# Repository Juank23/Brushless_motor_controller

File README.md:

# Brushless Motor Controller
This repository contains the hardware and software implementation of a brushless 
motor controller based on the [Espressif ESP32 module].

The schematic and PCB was designed using de EDA tool [KiCad] and all C++ 
code was compiled using the [Espressif ESP32 toolchain].

## Brushless Motor Controller Schematic
![][bm_controller_sch]

[bm_controller_sch]: https://github.com/fabriziotappero/Brushless_motor_controller/blob/master/PCB/bm_controller_sch.png ""
[Espressif ESP32 module]: https://www.espressif.com/en/products/hardware/development-boards
[Espressif ESP32 toolchain]: https://dl.espressif.com/doc/esp-idf/latest/index.html
[KiCad]: http://kicad-pcb.org/

## Hardware And Software Tools

Install **Kicad 5** on Debial-like Linux systems:
```
sudo add-apt-repository --yes ppa:js-reynaud/kicad-5
sudo apt-get update
sudo apt-get install kicad kicad-libraries
```

Install **ESP32 Espressif** compiler with its dependencies:
```
sudo apt-get install git wget make libncurses-dev flex bison gperf python python-serial

wget https://dl.espressif.com/dl/xtensa-esp32-elf-linux64-1.22.0-80-g6c4433a-5.2.0.tar.gz

tar -xvf xtensa-esp32-elf-linux64-1.22.0-80-g6c4433a-5.2.0.tar.gz
sudo mv xtensa-esp32-elf /opt
export PATH=/opt/xtensa-esp32-elf/bin:$PATH
```
Install the **ESP32 Espressif** developing environment IDF:
```
mkdir /opt/eps32 
cd /opt/eps32
git clone --recursive https://github.com/espressif/esp-idf.git
cd esp-idf
git submodule update --init
export IDF_PATH=/opt/esp32/esp-idf
```

Begin from a simple example:
```
git clone https://github.com/espressif/esp-idf-template.git myapp
cd myapp
make menuconfig
```
A lot of code examples in ```/opt/esp32/esp-idf/examples```. For more information refer to the [Espressif ESP32 Programming Guide]

[Espressif ESP32 Programming Guide]: https://dl.espressif.com/doc/esp-idf/latest/index.html

## References

[Espressif ESP32 Programming Guide](https://dl.espressif.com/doc/esp-idf/latest/index.html)

[Digi-Key An Introduction to Brushless DC Motor Control](https://www.digikey.com/en/articles/techzone/2013/mar/an-introduction-to-brushless-dc-motor-control)

## More Information
For any enquiry contact:

fabrizio.tappero@gmail.com

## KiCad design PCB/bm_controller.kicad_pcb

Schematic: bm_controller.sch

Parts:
C1, C2: 4.7uF; C_1210_3225Metric; Mouser 963-HMK325C7475MM-PE
C3: 1uF; C_0603_1608Metric
C4, C7: 0.01uF; C_0603_1608Metric
C5, C6: 22uF; C_0603_1608Metric; Mouser 810-C1608X5R1A226M
D1: V1PM15-M3/H; D_PowerDI-123; Mouser 78-V1PM15-M3/H
D2: APHD1608LCGCK; LED_0603_1608Metric; Mouser 604-APHD1608LCGCK
J1: Conn_01x08; PinSocket_1x08_P2.54mm_Vertical
J2: Conn_01x03; PinSocket_1x03_P2.54mm_Vertical
L1: 220uH; L_Taiyo-Yuden_NR-60xx; MPN VLS6045EX221MCA; Mouser 810-VLS6045EX221MCA
Q1: BSC040N10NS5; TDSON-8-1; Mouser 726-BSC040N10NS5
R1: 121k; R_0603_1608Metric
R2: 8.25k; R_0603_1608Metric
R3: 43.2k; R_0603_1608Metric
R4: 15k; R_0603_1608Metric
R5: 4.32k; R_0603_1608Metric
R6: 1M; R_0603_1608Metric
R7: 1k; R_0603_1608Metric
RV1: 100k; Potentiometer_Bourns_3214W_Vertical; Mouser 81-PVG3A104C01R00
TP1, TP2: none; TestPoint_Pad_D1.0mm
U1: ESP32-DOIT-EVALKIT
U2: IRS2890DS; SOIC-14_3.9x8.7mm_P1.27mm; Mouser 726-IRS2890DSTRPBF
U3: LM5017MR; SOIC-8-1EP_3.9x4.9mm_P1.27mm_EP2.35x2.35mm; MPN LM5017MRX/NOPB; Mouser 926-LM5017MRX/NOPB
U4: LMT87DCK; SOT-353_SC-70-5

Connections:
5V: C5.1, C6.1, L1.2, R4.2, RV1.1, TP2.1, U4.1, U4.4, U4.5
GND: C1.2, C2.2, C3.2, C5.2, C6.2, C7.1, R2.1, R5.1, R6.1, R7.1, RV1.3, U3.1, U3.9, U4.2
unnamed: C1.1, C2.1, D1.1, R1.2, R3.2, TP1.1, U3.2
unnamed: C3.1, U3.6
unnamed: C4.1, L1.1, U3.8
unnamed: C4.2, U3.7
unnamed: D2.1, R7.2
unnamed: D2.2, U1.20
unnamed: Q1.1 (S), Q1.2 (S), Q1.3 (S)
unnamed: R1.1, R2.2, U3.3
unnamed: R3.1, U3.4
unnamed: R4.1, R5.2, U3.5
Speed_Ref: C7.2, R6.2, RV1.2
Temp: U4.3
V_IN: D1.2

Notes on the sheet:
REFERENCES http://www.ti.com/tool/TIDA-00774 http://www.ti.com/lit/ug/tiducl0/tiducl0.pdf
5.37V, 500mA
MAIN 5V, 500mA DC/DC BUCK CONVERTER
1.2V
7.5V to 100V
0.6/1.2V

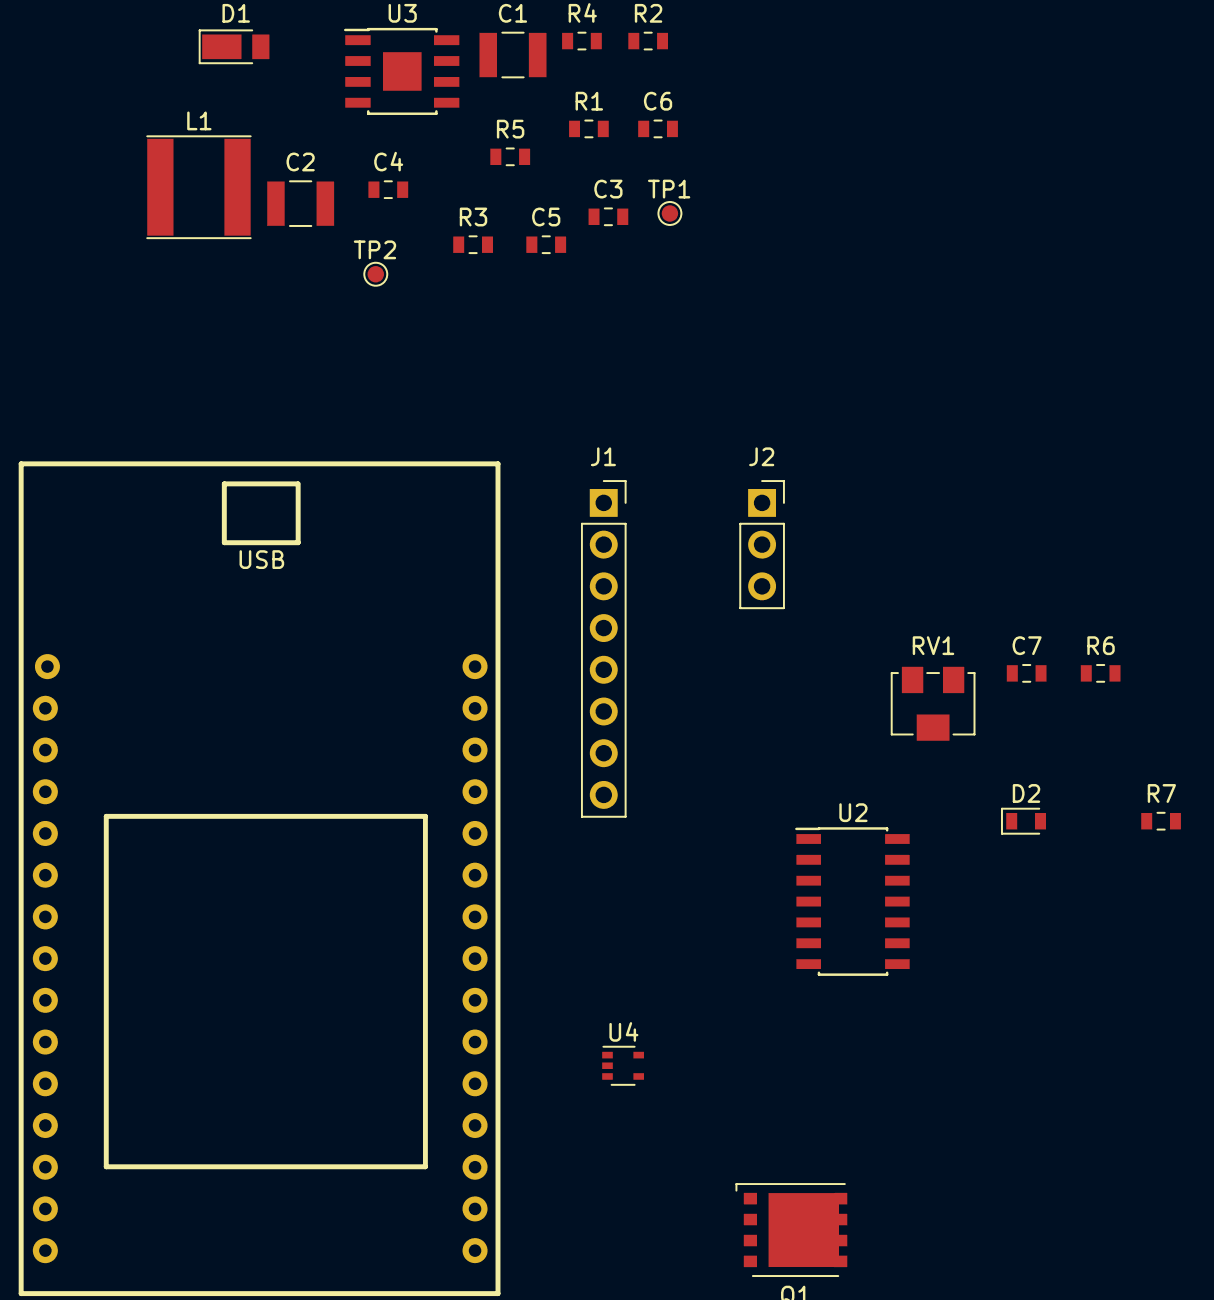
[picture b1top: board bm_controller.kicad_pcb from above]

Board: 2 copper layers, 27 parts (0 on the bottom side), 13 nets, no tracks yet.

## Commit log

2018-03-09 Better README file
2018-03-14 better README file and added schematic screenshot
2018-03-14 minor
2018-03-14 added gitignore, advanced with schematic design
